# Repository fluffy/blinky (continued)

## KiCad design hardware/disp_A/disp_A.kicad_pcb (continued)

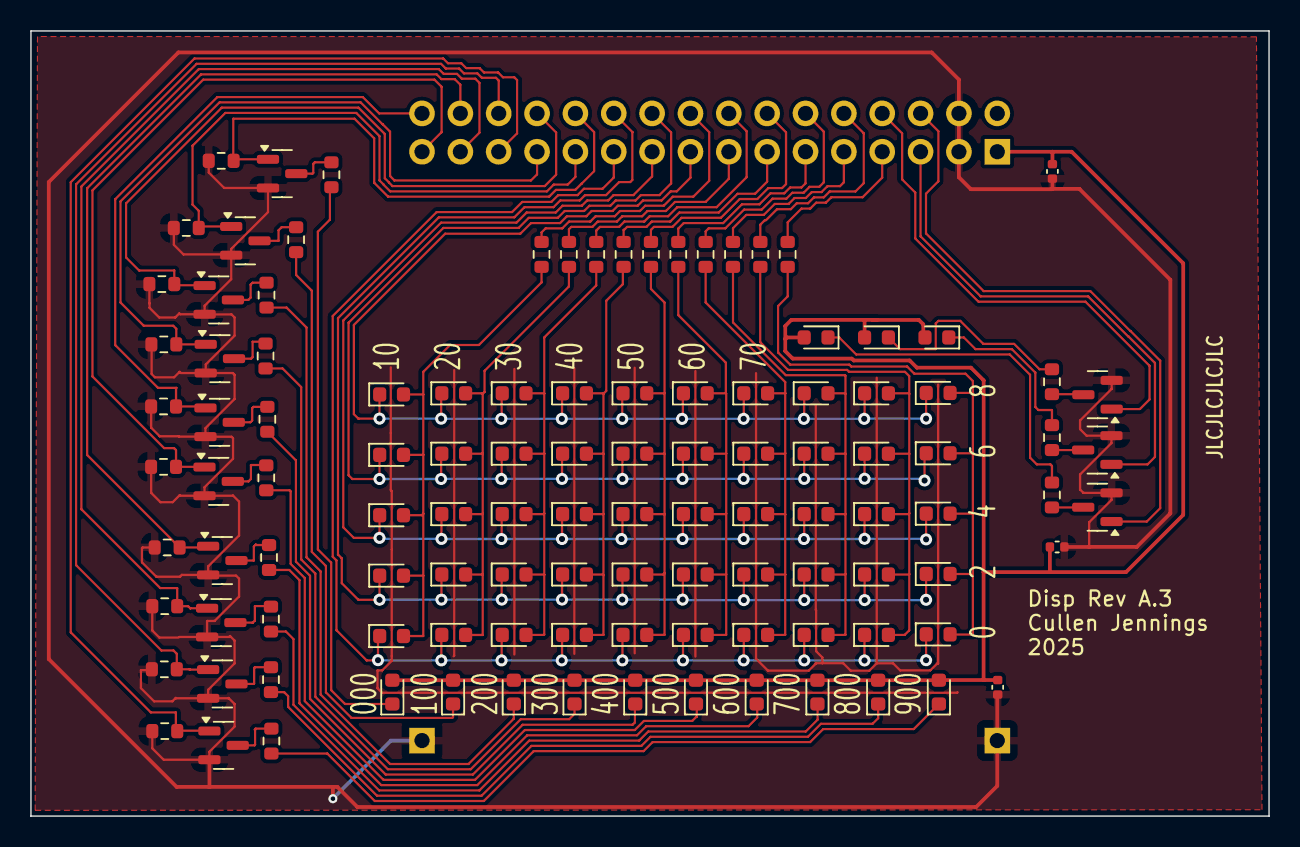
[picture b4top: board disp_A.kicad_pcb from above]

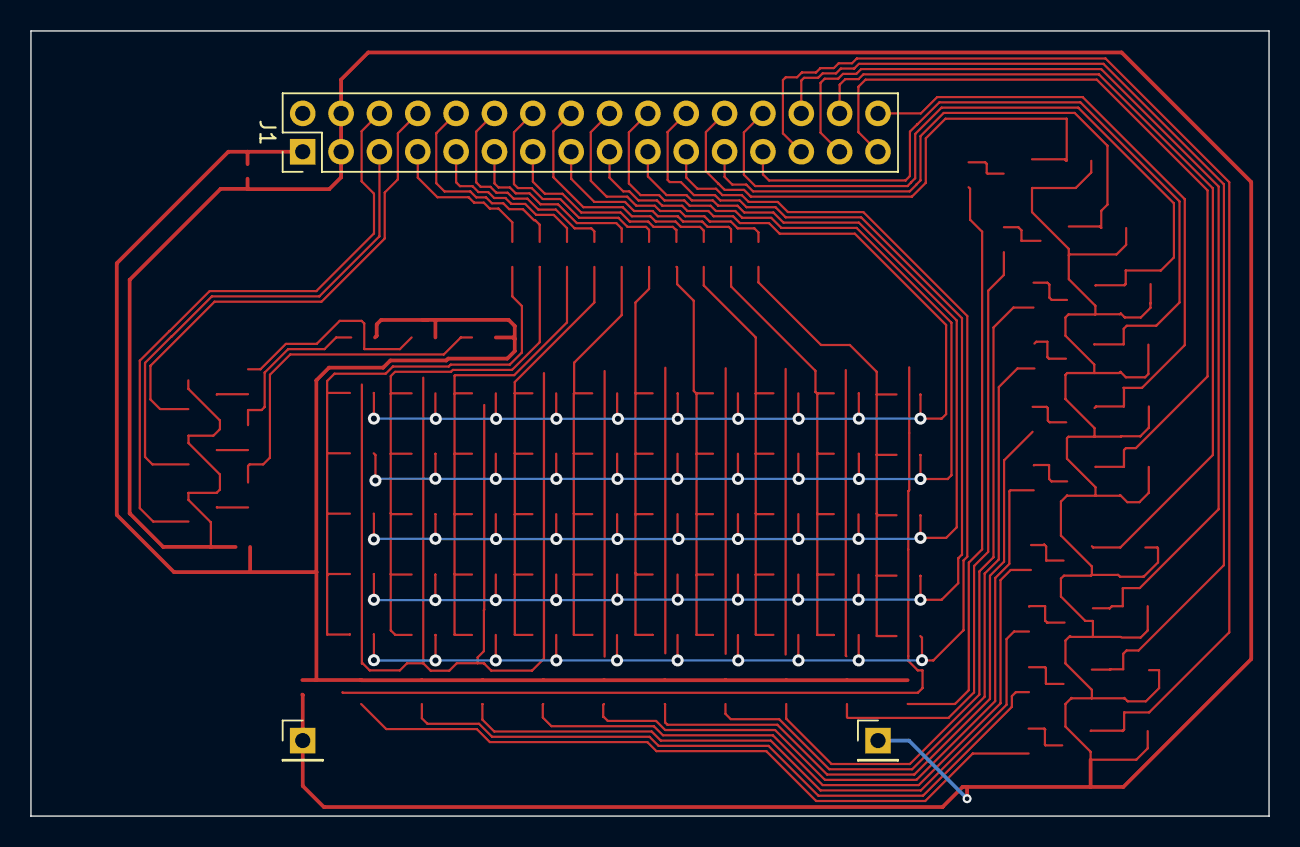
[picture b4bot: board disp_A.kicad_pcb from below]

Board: 2 copper layers, 82.0 x 52.0 mm, 115 parts (3 on the bottom side), 66 nets.

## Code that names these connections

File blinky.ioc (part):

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Mcu.Name=STM32F405RGTx
Mcu.Package=LQFP64
Mcu.UserName=STM32F405RGTx
PA0-WKUP.GPIOParameters=GPIO_Label
PA0-WKUP.GPIO_Label=AUX_CLK
PA0-WKUP.Signal=S_TIM5_CH1
PA1.GPIOParameters=GPIO_Label
PA1.GPIO_Label=AUX_GPS_PPS
PA1.Signal=S_TIM5_CH2
PA10.GPIOParameters=GPIO_Speed,GPIO_Label
PA10.GPIO_Label=USB_TX
PA10.GPIO_Speed=GPIO_SPEED_FREQ_HIGH
PA10.Mode=Asynchronous
PA10.Signal=USART1_RX
PA11.GPIOParameters=PinState,GPIO_Label
PA11.GPIO_Label=LEDMG
PA11.PinState=GPIO_PIN_SET
PA11.Signal=GPIO_Output
PA12.GPIOParameters=PinState,GPIO_Label
PA12.GPIO_Label=LEDMR
PA12.PinState=GPIO_PIN_RESET
PA12.Signal=GPIO_Output
PA13.GPIOParameters=GPIO_Label
PA13.GPIO_Label=SWDIO
PA13.Mode=Serial_Wire
PA13.Signal=SYS_JTMS-SWDIO
PA14.GPIOParameters=GPIO_Label
PA14.GPIO_Label=SWDCLK
PA14.Mode=Serial_Wire
PA14.Signal=SYS_JTCK-SWCLK
PA15.GPIOParameters=GPIO_Label
PA15.GPIO_Label=CLK
PA15.Signal=S_TIM2_CH1_ETR
PA2.GPIOParameters=GPIO_Label
PA2.GPIO_Label=AUX_SYNC_MON
PA2.Signal=S_TIM5_CH3
PA3.GPIOParameters=PinState,GPIO_PuPd,GPIO_Label
PA3.GPIO_Label=LED4
PA3.GPIO_PuPd=GPIO_NOPULL
PA3.PinState=GPIO_PIN_RESET
PA3.Signal=GPIO_Output
PA4.GPIOParameters=GPIO_Label
PA4.GPIO_Label=OSC_ADJ
PA4.Signal=COMP_DAC1_group
PA5.GPIOParameters=GPIO_Label
PA5.GPIO_Label=AUD_OUT
PA5.Signal=COMP_DAC2_group
PA6.GPIOParameters=GPIO_Label
PA6.GPIO_Label=LED1
PA6.Signal=GPIO_Output
PA7.GPIOParameters=GPIO_Label
PA7.GPIO_Label=LED2
PA7.Signal=ADCx_IN7
PA8.GPIOParameters=GPIO_Label
PA8.GPIO_Label=SYNC_OUT
PA8.Signal=S_TIM1_CH1
PA9.GPIOParameters=GPIO_Speed,GPIO_Label
PA9.GPIO_Label=USB_RX
PA9.GPIO_Speed=GPIO_SPEED_FREQ_HIGH
PA9.Mode=Asynchronous
PA9.Signal=USART1_TX
PB0.GPIOParameters=PinState,GPIO_Label
PB0.GPIO_Label=LED9
PB0.PinState=GPIO_PIN_SET
PB0.Signal=GPIO_Output
PB1.GPIOParameters=PinState,GPIO_Label
PB1.GPIO_Label=LED10
PB1.PinState=GPIO_PIN_SET
PB1.Signal=GPIO_Output
PB10.GPIOParameters=GPIO_Label
PB10.GPIO_Label=GPS_PPS
PB10.Signal=S_TIM2_CH3
PB11.GPIOParameters=GPIO_Label
PB11.GPIO_Label=SYNC_MON
PB11.Signal=S_TIM2_CH4
PB12.GPIOParameters=GPIO_Label
PB12.GPIO_Label=NCOL8
PB12.Signal=GPIO_Output
PB13.GPIOParameters=GPIO_Label
PB13.GPIO_Label=NCOL7
PB13.Signal=GPIO_Output
PB14.GPIOParameters=GPIO_Label
PB14.GPIO_Label=NCOL6
PB14.Signal=GPIO_Output
PB15.GPIOParameters=GPIO_Label
PB15.GPIO_Label=NCOL5
PB15.Signal=GPIO_Output
PB2.GPIOParameters=GPIO_PuPd,GPIO_Label
PB2.GPIO_Label=BOOT1
PB2.GPIO_PuPd=GPIO_PULLDOWN
PB2.Signal=GPIO_Input
PB3.GPIOParameters=GPIO_Label
PB3.GPIO_Label=SYNC_IN
PB3.Signal=S_TIM2_CH2
PB4.GPIOParameters=GPIO_PuPd,GPIO_Label
PB4.GPIO_Label=LED3
PB4.GPIO_PuPd=GPIO_PULLDOWN
PB4.Signal=GPIO_Input
PB5.GPIOParameters=GPIO_Speed,GPIO_Label
PB5.GPIO_Label=NROW5
PB5.GPIO_Speed=GPIO_SPEED_FREQ_LOW
PB5.Signal=GPIO_Output
PB6.GPIOParameters=GPIO_Label
PB6.GPIO_Label=NCOL1
PB6.Signal=GPIO_Output
PB7.GPIOParameters=GPIO_Label
PB7.GPIO_Label=LEDMB
PB7.Signal=GPIO_Output
PB8.GPIOParameters=GPIO_Label
PB8.GPIO_Label=SCL
PB8.Mode=I2C
PB8.Signal=I2C1_SCL
PB9.GPIOParameters=GPIO_Label
PB9.GPIO_Label=SDA
PB9.Mode=I2C
PB9.Signal=I2C1_SDA
PC0.GPIOParameters=GPIO_Label
PC0.GPIO_Label=AUD_IN
PC0.Signal=ADCx_IN10
PC1.GPIOParameters=GPIO_Label
PC1.GPIO_Label=NROW2
PC1.Signal=GPIO_Output
PC10.GPIOParameters=GPIO_Speed,GPIO_Label
PC10.GPIO_Label=GPS_RX1
PC10.GPIO_Speed=GPIO_SPEED_FREQ_HIGH
PC10.Mode=Asynchronous
PC10.Signal=USART3_TX
PC11.GPIOParameters=GPIO_Speed,GPIO_Label
PC11.GPIO_Label=GPS_TX1
PC11.GPIO_Speed=GPIO_SPEED_FREQ_HIGH
PC11.Mode=Asynchronous
PC11.Signal=USART3_RX
PC12.GPIOParameters=GPIO_Speed,GPIO_Label
PC12.GPIO_Label=NCOL9
PC12.GPIO_Speed=GPIO_SPEED_FREQ_LOW
PC12.Signal=GPIO_Output
PC13-ANTI_TAMP.GPIOParameters=GPIO_PuPd,GPIO_Label
PC13-ANTI_TAMP.GPIO_Label=BTN1
PC13-ANTI_TAMP.GPIO_PuPd=GPIO_PULLDOWN
PC13-ANTI_TAMP.Signal=GPIO_Input
PC14-OSC32_IN.GPIOParameters=PinState,GPIO_PuPd,GPIO_Label
PC14-OSC32_IN.GPIO_Label=NCOL10
PC14-OSC32_IN.GPIO_PuPd=GPIO_NOPULL
PC14-OSC32_IN.PinState=GPIO_PIN_RESET
PC14-OSC32_IN.Signal=GPIO_Output
PC15-OSC32_OUT.GPIOParameters=PinState,GPIO_PuPd,GPIO_Label
PC15-OSC32_OUT.GPIO_Label=NROW1
PC15-OSC32_OUT.GPIO_PuPd=GPIO_NOPULL
PC15-OSC32_OUT.PinState=GPIO_PIN_RESET
PC15-OSC32_OUT.Signal=GPIO_Output
PC2.GPIOParameters=GPIO_Label
PC2.GPIO_Label=NROW3
PC2.Signal=GPIO_Output
PC3.GPIOParameters=GPIO_Label
PC3.GPIO_Label=NROW4
PC3.Signal=GPIO_Output
PC4.GPIOParameters=GPIO_Label
PC4.GPIO_Label=LED7
PC4.Signal=GPIO_Output
PC5.GPIOParameters=PinState,GPIO_Label
PC5.GPIO_Label=LED8
PC5.PinState=GPIO_PIN_SET
PC5.Signal=GPIO_Output
PC6.GPIOParameters=GPIO_Label
PC6.GPIO_Label=AUX_SYNC_IN
PC6.Signal=S_TIM8_CH1
PC7.GPIOParameters=GPIO_Label
PC7.GPIO_Label=NCOL4
PC7.Signal=GPIO_Output
PC8.GPIOParameters=GPIO_Label
PC8.GPIO_Label=NCOL3
PC8.Signal=GPIO_Output
PC9.GPIOParameters=GPIO_Label
PC9.GPIO_Label=NCOL2
PC9.Signal=GPIO_Output
PD2.GPIOParameters=GPIO_Speed,GPIO_Label
PD2.GPIO_Label=DB3
PD2.GPIO_Speed=GPIO_SPEED_FREQ_HIGH
PD2.Signal=GPIO_Output
PH0-OSC_IN.GPIOParameters=GPIO_Label
PH0-OSC_IN.GPIO_Label=HSE_IN
PH0-OSC_IN.Mode=HSE-External-Oscillator
PH0-OSC_IN.Signal=RCC_OSC_IN
PH1-OSC_OUT.GPIOParameters=GPIO_Label
PH1-OSC_OUT.GPIO_Label=HSE_OUT
PH1-OSC_OUT.Mode=HSE-External-Oscillator
PH1-OSC_OUT.Signal=RCC_OSC_OUT
RCC.HSE_VALUE=16000000
RCC.SYSCLKFreq_VALUE=168000000
RCC.SYSCLKSource=RCC_SYSCLKSOURCE_PLLCLK
board=custom

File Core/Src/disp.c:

// SPDX-FileCopyrightText: Copyright (c) 2023 Cullen Jennings
// SPDX-License-Identifier: BSD-2-Clause

#include "disp.h"

#include <stdbool.h>
#include <stdint.h>
#include <stdio.h>
#include <stm32f4xx_ll_tim.h>
#include <string.h>

#include "config.h"
#include "hardware.h"
#include "main.h"
#include "measurement.h"
#include "setting.h"

void dispInit() {
  // nothing to do here
}

void dispSetup() {
  if (config.product != 1) {
    return;
  }

  GPIO_InitTypeDef GPIO_InitStruct = {0};

  HAL_GPIO_DeInit(LED2_GPIO_Port, LED2_Pin);
  GPIO_InitStruct.Pin = LED2_Pin;
  GPIO_InitStruct.Mode = GPIO_MODE_OUTPUT_PP;
  GPIO_InitStruct.Pull = GPIO_NOPULL;
  GPIO_InitStruct.Speed = GPIO_SPEED_FREQ_LOW;
  HAL_GPIO_Init(LED2_GPIO_Port, &GPIO_InitStruct);

  HAL_GPIO_DeInit(LED3_GPIO_Port, LED3_Pin);
  GPIO_InitStruct.Pin = LED3_Pin;
  GPIO_InitStruct.Mode = GPIO_MODE_OUTPUT_PP;
  GPIO_InitStruct.Pull = GPIO_NOPULL;
  GPIO_InitStruct.Speed = GPIO_SPEED_FREQ_LOW;
  HAL_GPIO_Init(LED3_GPIO_Port, &GPIO_InitStruct);

  HAL_GPIO_DeInit(LED5_GPIO_Port, LED5_Pin);
  GPIO_InitStruct.Pin = LED5_Pin;
  GPIO_InitStruct.Mode = GPIO_MODE_OUTPUT_PP;
  GPIO_InitStruct.Pull = GPIO_NOPULL;
  GPIO_InitStruct.Speed = GPIO_SPEED_FREQ_LOW;
  HAL_GPIO_Init(LED5_GPIO_Port, &GPIO_InitStruct);

  HAL_GPIO_DeInit(LED6_GPIO_Port, LED6_Pin);
  GPIO_InitStruct.Pin = LED6_Pin;
  GPIO_InitStruct.Mode = GPIO_MODE_OUTPUT_PP;
  GPIO_InitStruct.Pull = GPIO_NOPULL;
  GPIO_InitStruct.Speed = GPIO_SPEED_FREQ_LOW;
  HAL_GPIO_Init(LED6_GPIO_Port, &GPIO_InitStruct);

  HAL_GPIO_WritePin(LED1_GPIO_Port, LED1_Pin, GPIO_PIN_RESET);
  HAL_GPIO_WritePin(LED2_GPIO_Port, LED2_Pin, GPIO_PIN_RESET);
  HAL_GPIO_WritePin(LED3_GPIO_Port, LED3_Pin, GPIO_PIN_RESET);
  HAL_GPIO_WritePin(LED4_GPIO_Port, LED4_Pin, GPIO_PIN_RESET);
#if 1  // TODO - still no use onv v10hw
  HAL_GPIO_WritePin(LED5_GPIO_Port, LED5_Pin, GPIO_PIN_RESET);
  HAL_GPIO_WritePin(LED6_GPIO_Port, LED6_Pin, GPIO_PIN_RESET);
#endif
  HAL_GPIO_WritePin(LED7_GPIO_Port, LED7_Pin, GPIO_PIN_RESET);
  HAL_GPIO_WritePin(LED8_GPIO_Port, LED8_Pin, GPIO_PIN_RESET);
  HAL_GPIO_WritePin(LED9_GPIO_Port, LED9_Pin, GPIO_PIN_RESET);
  HAL_GPIO_WritePin(LED10_GPIO_Port, LED10_Pin, GPIO_PIN_RESET);
}

void dispUpdate(int32_t dispUs, int32_t dispS) {
  if (config.product != 1) {
    return;
  }

  // called in an interupt - keep this fast
  int32_t ledMs = dispUs / 1000l;

  if (setting.blinkDispAudio) {
    ledMs = data.blinkAudioDelayMs;
  }

  if (ledMs >= 1000) {
    ledMs -= 1000;
  }

#if 0
    // this shows 2 ms times to 1 second
    int16_t binCount =  1  << (9 - (ledMs / 100)%10) ;  // 100 ms
    int row = 5 - (ledMs / 2) % 5;     // 2 ms across
    int col = 10 - (ledMs / 10) % 10;  // 10 ms down
#else
  // this shows 30 * 4 fps frame times
  int blinks = (ledMs * 3);                            // 3000 blinks per second
  int16_t binCount = 1 << (9 - (blinks / 1000) % 10);  // 3 fps
  int row = 5 - (blinks / 25) % 4;                     // 120 fps across 4 leds
  int col = 10 - (blinks / 100) % 10;                  // 30 fps
#endif

  if (setting.blinkBlank) {
    binCount = 0x1000;
    row = 255;
    col = 255;
  }

  if (setting.blinkHaveDisplay) {
    HAL_GPIO_WritePin(NCOL1_GPIO_Port, NCOL1_Pin,
                      (col == 1) ? GPIO_PIN_SET : GPIO_PIN_RESET);
    HAL_GPIO_WritePin(NCOL2_GPIO_Port, NCOL2_Pin,
                      (col == 2) ? GPIO_PIN_SET : GPIO_PIN_RESET);
    HAL_GPIO_WritePin(NCOL3_GPIO_Port, NCOL3_Pin,
                      (col == 3) ? GPIO_PIN_SET : GPIO_PIN_RESET);
    HAL_GPIO_WritePin(NCOL4_GPIO_Port, NCOL4_Pin,
                      (col == 4) ? GPIO_PIN_SET : GPIO_PIN_RESET);
    HAL_GPIO_WritePin(NCOL5_GPIO_Port, NCOL5_Pin,
                      (col == 5) ? GPIO_PIN_SET : GPIO_PIN_RESET);
    HAL_GPIO_WritePin(NCOL6_GPIO_Port, NCOL6_Pin,
                      (col == 6) ? GPIO_PIN_SET : GPIO_PIN_RESET);
    HAL_GPIO_WritePin(NCOL7_GPIO_Port, NCOL7_Pin,
                      (col == 7) ? GPIO_PIN_SET : GPIO_PIN_RESET);
    HAL_GPIO_WritePin(NCOL8_GPIO_Port, NCOL8_Pin,
                      (col == 8) ? GPIO_PIN_SET : GPIO_PIN_RESET);
    HAL_GPIO_WritePin(NCOL9_GPIO_Port, NCOL9_Pin,
                      (col == 9) ? GPIO_PIN_SET : GPIO_PIN_RESET);
    HAL_GPIO_WritePin(NCOL10_GPIO_Port, NCOL10_Pin,
                      (col == 10) ? GPIO_PIN_SET : GPIO_PIN_RESET);

    HAL_GPIO_WritePin(NROW1_GPIO_Port, NROW1_Pin,
                      (row == 1) ? GPIO_PIN_RESET : GPIO_PIN_SET);
    HAL_GPIO_WritePin(NROW2_GPIO_Port, NROW2_Pin,
                      (row == 2) ? GPIO_PIN_RESET : GPIO_PIN_SET);
    HAL_GPIO_WritePin(NROW3_GPIO_Port, NROW3_Pin,
                      (row == 3) ? GPIO_PIN_RESET : GPIO_PIN_SET);
    HAL_GPIO_WritePin(NROW4_GPIO_Port, NROW4_Pin,
                      (row == 4) ? GPIO_PIN_RESET : GPIO_PIN_SET);
    HAL_GPIO_WritePin(NROW5_GPIO_Port, NROW5_Pin,
                      (row == 5) ? GPIO_PIN_RESET : GPIO_PIN_SET);
  }

  if (setting.blinkHaveDisplay) {
    // Low 4 bits of display
    HAL_GPIO_WritePin(LED1_GPIO_Port, LED1_Pin,
                      (binCount & 0x01) ? GPIO_PIN_SET : GPIO_PIN_RESET);
    HAL_GPIO_WritePin(LED2_GPIO_Port, LED2_Pin,
                      (binCount & 0x02) ? GPIO_PIN_SET : GPIO_PIN_RESET);
    HAL_GPIO_WritePin(LED3_GPIO_Port, LED3_Pin,
                      (binCount & 0x04) ? GPIO_PIN_SET : GPIO_PIN_RESET);
    HAL_GPIO_WritePin(LED4_GPIO_Port, LED4_Pin,
                      (binCount & 0x08) ? GPIO_PIN_SET : GPIO_PIN_RESET);

    // High 4 bits of display
#if 1  // TODO - still not use on V10 hw
    // problems LED 5,6 input only
    HAL_GPIO_WritePin(LED5_GPIO_Port, LED5_Pin,
                      (binCount & 0x10) ? GPIO_PIN_SET : GPIO_PIN_RESET);
    HAL_GPIO_WritePin(LED6_GPIO_Port, LED6_Pin,
                      (binCount & 0x20) ? GPIO_PIN_SET : GPIO_PIN_RESET);
#endif

    HAL_GPIO_WritePin(LED7_GPIO_Port, LED7_Pin,
                      (binCount & 0x40) ? GPIO_PIN_SET : GPIO_PIN_RESET);
    HAL_GPIO_WritePin(LED8_GPIO_Port, LED8_Pin,
                      (binCount & 0x80) ? GPIO_PIN_SET : GPIO_PIN_RESET);

    HAL_GPIO_WritePin(LED9_GPIO_Port, LED9_Pin,
                      (binCount & 0x100) ? GPIO_PIN_SET : GPIO_PIN_RESET);
    HAL_GPIO_WritePin(LED10_GPIO_Port, LED10_Pin,
                      (binCount & 0x200) ? GPIO_PIN_SET : GPIO_PIN_RESET);
  }
}

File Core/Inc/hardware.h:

// SPDX-FileCopyrightText: Copyright (c) 2023 Cullen Jennings
// SPDX-License-Identifier: BSD-2-Clause

#pragma once

#include <stm32f4xx_ll_tim.h>

extern I2C_HandleTypeDef hi2c1;

extern TIM_HandleTypeDef htim1;
extern TIM_HandleTypeDef htim2;
extern TIM_HandleTypeDef htim3;
extern TIM_HandleTypeDef htim4;
extern TIM_HandleTypeDef htim5;
extern TIM_HandleTypeDef htim6;
extern TIM_HandleTypeDef htim8;

extern UART_HandleTypeDef huart1;
extern UART_HandleTypeDef huart3;

extern ADC_HandleTypeDef hadc1;
extern ADC_HandleTypeDef hadc2;
extern DAC_HandleTypeDef hdac;

#define hADC hadc1

#define hDAC hdac
#define DAC_CH_OSC_ADJ DAC_CHANNEL_1
#define DAC_CH_AUD_OUT DAC_CHANNEL_2

#define hI2c hi2c1
#define hUartDebug huart1
#define hUartGps huart3
#define USART_GPS USART3

#define hTimePps htim1
#define TimePps_CH_SYNC_OUT TIM_CHANNEL_1
#define TimePps_LL_CH_SYNC_OUT LL_TIM_CHANNEL_CH1

#define hTimeSync htim2
#define TimeSync_CH_SYNC_IN TIM_CHANNEL_2
#define TimeSync_HAL_CH_SYNC_IN HAL_TIM_ACTIVE_CHANNEL_2
#define TimeSync_CH_GPS_PPS TIM_CHANNEL_3
#define TimeSync_HAL_CH_GPS_PPS HAL_TIM_ACTIVE_CHANNEL_3
#define TimeSync_CH_SYNC_MON TIM_CHANNEL_4
#define TimeSync_HAL_CH_SYNC_MON HAL_TIM_ACTIVE_CHANNEL_4

#define hTimeADC htim3

#define hTimeBlink htim4

#define hTimeAux htim5
#define TimeAux_CH_AUX_CLK TIM_CHANNEL_1
#define TimeAux_CH_GPS_PPS TIM_CHANNEL_2
#define TimeAux_HAL_CH_GPS_PPS HAL_TIM_ACTIVE_CHANNEL_3
#define TimeAux_CH_SYNC_MON TIM_CHANNEL_3
#define TimeAux_HAL_CH_SYNC_MON HAL_TIM_ACTIVE_CHANNEL_3

#define hTimeDAC htim6

#define hTimeLtc htim8
#define TimeLtc_CH_SYNC_IN2 TIM_CHANNEL_1
#define TimeLtc_HAL_CH_SYNC_IN2 HAL_TIM_ACTIVE_CHANNEL_1

#define LED6_Pin GPS_RX1_Pin
#define LED6_GPIO_Port GPS_RX1_GPIO_Port
#define LED5_Pin GPS_TX1_Pin
#define LED5_GPIO_Port GPS_TX1_GPIO_Port
#define BTN2_Pin GPS_PPS_Pin
#define BTN2_GPIO_Port GPS_PPS_GPIO_Port
#define BTN3_Pin BOOT1_Pin
#define BTN3_GPIO_Port BOOT1_GPIO_Port

void Error_Handler();

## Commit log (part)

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2023-12-30 set up eeprom form serial #9
2023-12-30 print phases of inputs
2023-12-30 clean up time print display and sync
2023-12-30 update version
2023-12-30 clean up formatting
2023-12-30 long history for ppb
2024-01-01 redo version
2024-01-02 clean up sync and calculating total seconds
2024-01-03 program board serial #10
2024-01-03 up version
2024-01-04 update stm32flash line to be correct
2024-01-04 update printouts
2024-01-04 update CH340 datasheet to english
2024-01-04 cleanup existing schematic
2024-01-04 start new switch regulator layout
2024-01-05 start 2nd supply
2024-01-05 clean up
2024-01-05 add yet antoehr power connector
2024-01-05 send off 9.3 version of power board
2024-01-05 gps sync going
2024-01-05 sync to PPS input
2024-01-05 sync LTC with GPS
2024-01-05 ltc time synced up in and out
2024-01-05 refactor case
2024-01-05 reflow
2024-01-05 sync ext when have gps or ltc
2024-01-05 set status LED based on sync
2024-01-05 validate sync
2024-01-06 start debug of problem where get out of sync for a cycle
2024-01-06 start 9.4 power supply test
2024-01-06 clean up simple 9.4 for new power supply
2024-01-06 do v9.4 board with new power reg
2024-01-06 submitted version of 9.4 board
2024-01-07 Fix bug with loosing last transition of LTC
2024-01-07 turn off broken ppm and pbm code
2024-01-07 added PPS mode
2024-01-07 new config format with space for PPS mode config
2024-01-07 updated calbration for v9 boards
2024-01-07 fix clock 9.4 for rotations that JLCPCB found after I submitted
2024-01-08 add .editorconfig
2024-01-09 migrate to latest cube
2024-01-09 changes to move to cmake
2024-01-09 remove old make stuff
2024-01-09 add openocd open ocd open-ocd config file
2024-01-10 clean up detection of having sync and loosing sync
2024-01-10 update readme for cmake
2024-01-10 upgrade clion
2024-01-10 start clock v10.0
2024-01-10 start disp V10.0 HW
2024-01-10 start blink 10.0 hw
2024-01-10 Fixes #259 pwrd on gpx rx
2024-01-10 Fixes #211 led setting when not running
2024-01-11 change temp sensor to to TMP112A
2024-01-12 change LEDMY to LEDMB. Fixes #230
2024-01-13 update version and ingores
2024-01-13 update calbration for #7 with 2Mhz osc
2024-01-13 update syncValidTimeSeconds
2024-01-13 add datashee for oven controlled oscilator
2024-01-14 add design for box ends
2024-01-15 start seperation of disp code
2024-01-15 seperate out disp code
2024-01-15 fix up setting linking
2024-01-21 update to fix link problems from refactor
2024-01-21 update for serial program
2024-01-22 update serial program notes
2024-01-23 clean up LED5/6 problem and BTN2
2024-01-23 fix buttons. Fixes #264 Fixes #261
2024-01-23 fix up layout on clock
2024-01-23 add current sense resistor to clock 3.3V
2024-01-23 add a sense resistor to blink v10
2024-01-23 add sense resitors to other ps on bink
2024-01-24 replace power selection diodes with ideal diodes
2024-01-24 start adding reset circuit to v10 blink
2024-01-24 start adding boost powere supply
2024-01-25 sorting out blink 10 schematic
2024-01-25 starting part placment blink 10
2024-01-25 update reset boot on clock v10
2024-01-25 fix up ground on clock v10
2024-01-26 Add PP/LTC Jumper Fixes #275
2024-01-26 add power sense resisitors Fixes #294
2024-01-26 add jumper for USB / Reset disconnect Fixes #293
2024-01-26 moved to 250mW resisotrs. Fixes #289
2024-01-26 fiux voltage dirvide for GPS TX. Fixes #260
2024-01-26 update version with CLion
2024-01-26 fix up clock board errors
2024-01-27 route blink v10 board
2024-01-27 clean up PCB
2024-01-27 clean up blink pcb
2024-01-27 blink board ready for v10
2024-01-28 version of blink submitted for hw v10.0
2024-01-28 version submitted of disp v10.0 hardware
2024-01-28 remove the connector offset
2024-01-28 add pins for other osc
2024-01-28 thicker 5V power distribution
2024-01-28 clean up clock v10 PCB
2024-01-28 version of clock harrdware V10.0
2024-01-28 update wishlist
2024-01-29 update with production pick and place changes
2024-01-30 adjust version
2024-01-30 add SPDX headers
2024-02-01 start blink v11 hw
2024-02-02 start clock v11 hw
2024-02-06 start changes for V10 clock pin outs
2024-02-06 more changes for V10 clock pins
2024-02-06 add 2nd ADC for USB power sense
2024-02-06 fix tyupo
2024-02-06 add todo
2024-02-06 updating pins
2024-02-06 move button conde to it's own file
2024-02-07 start adding power managment
2024-02-09 move phase info into settings
2024-02-09 move clock ration settings into settings
2024-02-09 program serial number 13
2024-02-09 fix typo
2024-02-09 fix but on adc1 for power detection
2024-02-09 correctly detect USB power available
2024-02-10 update power handling
2024-02-10 start of blink v10 config
2024-02-10 add deinit to buttons
2024-02-10 correct pin names
2024-02-10 buttons working on display board
2024-02-10 disp working v10 blink hw
2024-02-10 initalize clock board #15
2024-02-10 setup gps serial on clock board
2024-02-12 make clock board USB power only. Fixes #307
2024-02-13 update clock serial 15 to have oxco
2024-02-13 Remove R49. Fixes #303
2024-02-13 remove needless pull down reistors. Fixes #304
2024-02-15 update with sockets for differnt oscilators
2024-02-16 chance current sense resistor. Fixes#308
2024-02-18 cleaning up board
2024-02-18 clean up pcb to make more room
2024-02-19 more board cleanup
2024-02-20 start adding battery under voltageprotection UVP
2024-02-20 adding battery protection
2024-02-20 clean up for move of cpu
2024-02-21 made space for battery
2024-02-21 add test points for battery protection
2024-02-21 swap sync in / pps out
2024-02-21 fix up footprints
2024-02-22 add GPS hdr to clock board
2024-02-22 blink V11 hw hardware send to production
2024-02-22 fix rotations on blink hw V11
2024-02-23 start reorg of connectors on clock
2024-02-23 add switch to clock
2024-02-23 fixing up routing on clock
2024-02-24 clean up board
2024-02-24 update to latest CubeMX
2024-02-25 clean up clcok schematic
2024-02-25 add mount holes to clock
2024-02-25 fixed mult osc symbol error
2024-02-25 production version of clock V11 hardware
2024-02-25 start GPS variant of clock board
2024-02-25 hardsare V11 GPS board to production
2024-02-26 location confirmation for JLCPCB
2024-02-29 configured clock ev11 board ser16
2024-03-05 setup software config for GPS board
2024-03-05 add auto sync for GPS board. Fixes #312
2024-03-05 update readme for V11
2024-03-06 switch to ocxo testing
2024-03-06 fix tty to cu
2024-03-06 read LTC/PPS mode jumper
2024-03-07 move to TXCO
2024-03-08 testing battery
2024-03-10 start move to kicad8
2024-03-10 start v12 of clock and gps in kicad8
2024-03-12 start box ends in freecad
2024-03-12 ignore freecad backup files
2024-03-12 basic back end of blink box in freecad
2024-03-12 start edge cut out sides
2024-03-12 add drwawing
2024-03-25 add corner radius
2024-03-28 blink box test print 1
2024-03-28 update for correct size side offsets
2024-03-28 change view
2024-03-28 v2 print
2024-03-28 start readme for box
2024-03-30 start front of blink box
2024-03-30 add front mount holes
2024-03-30 add 3d step model export for V12 blink
2024-03-30 updates for 3d render
2024-04-01 update box
2024-04-03 fix symbol for USBLC6-2P6 that seems chaged in kicad 8
2024-04-03 fix up schematic for new USBLC6-2P6 footprint
2024-04-03 fix error on PCB from kicad8
2024-04-03 fix warnings from kicad8
2024-04-03 remove the battery protection circuit
2024-04-03 move USB connecro out 2 mm
2024-04-03 move LED over
2024-04-03 moved the test points off rails
2024-04-04 fix rotations for V12 blink
2024-04-04 blink v12 hw submitted
2024-04-05 clean up 3D files for blink board
2024-04-05 add 3D model for USB connector
2024-04-05 add 3D model for LED
2024-04-06 fixed offset for JLCPCB
2024-04-06 clean up gitignore
2024-04-09 update clock_v12 to kicad 8
2024-04-09 update on clock for kicad 8
2024-04-09 move USB on clock v12
2024-04-09 clean up 3d models for clock
2024-04-10 replace tanntium caps and start blink v13
2024-04-10 clean up version for blink v13
2024-04-14 format eeprome Serial #21 EV12 board
2024-04-14 format eeprome Serial #22 EV12 board
2024-04-27 update #21 and #22 to have TCXO
2024-04-30 updated exported pcb 3d model
2024-04-30 seperate adjustment for fron BNC offset
2024-04-30 export 3d print of parts
2024-04-30 print project for bambu
2024-05-01 adjusted hole locations
2024-05-08 update box with drawing
2024-05-10 update sizes
2024-05-11 add xcs laser file
2024-05-13 start to rename
2024-05-13 rename box file
2024-05-13 rename parts of box
2024-05-13 remove old fusion 360 files box
2024-05-13 remove old generated 3d files
2024-05-13 generated views for blink box
2024-05-13 update box readme
2024-05-14 move blink board to start RevA
2024-05-14 generate production files for blink RevA
2024-05-14 remove old versions
2024-05-15 move clock board to Rev A
2024-05-15 moved RJ45 out 2mm
2024-05-15 updarte production files for Clock board
2024-05-15 start GPS A
2024-05-15 move RJ45 on gps
2024-05-15 typo
2024-05-17 update design
2024-05-18 update JST PH S3B connector with 3D model
2024-05-18 update 3d model for 5v power reg
2024-05-18 start box for clock
2024-05-20 start edit front of clock box
2024-05-20 more edits on clock box
2024-05-21 add slot for prog connector
2024-05-22 rough outline for front place done
2024-05-22 start RJ45 location
2024-05-25 add RJ45 to clock box
2024-05-25 add USB connector slot to clock box
2024-05-25 tune up box hole locations
2024-05-26 generate the prod files for box
2024-05-26 setting up laser files
2024-05-26 update dxf files
2024-05-26 add labels
2024-05-26 set up and laser cut
2024-05-26 setup up Clock Rev A for build
2024-05-26 start Disp rev A
2024-05-26 remove old hardware files
2024-05-26 generate production files for disp board Rev A
2024-05-27 updade clock order with correct diode. Fixes #339
2024-05-27 update footprints
2024-05-27 start generation of GPS rev A.1 production files
2024-05-27 update exceptions
2024-05-27 version of GPS Rev A.1 submitted to JLCPCB
2024-05-27 updated blink productions files
2024-05-27 start hardware notes
2024-05-27 remove tal caps on GPS, clean up schamatic
2024-05-27 updadte osc footprint to use one with mount holes
2024-05-27 start making parts list for device
2024-05-27 clean up bom format
2024-05-28 fix RJ45 size in box and regen the prod files for clockA box
2024-05-28 tune up locations of wholes in blink boxA
2024-05-28 update tools in readme
2024-05-28 regen the blinkA box prod files
2024-05-28 start GpsA box
2024-05-28 generate GpsA box prod files
2024-05-28 move to one laser files for all ends
2024-05-28 update laser with updated connector locations
2024-05-29 flip blank/mute labels
2024-05-30 tune up location of holes in frames
2024-05-31 update bom list
2024-05-31 adjusted cut speeds
2024-05-31 update laser file for cut take #3
2024-05-31 get local changes
2024-05-31 set cut paramters
2024-06-09 adjust hight of USB and RJ45
2024-06-09 adding serial numbers to new boards
2024-06-09 moving blink to V A.1
2024-06-10 update blinky
2024-06-10 rename readme
2024-06-10 regen clock box prod files
2024-06-10 regen blink box prod files
2024-06-10 regen gps box prod files
2024-06-11 regen files for blink
2024-06-13 add JLC part confirmation images for blink Rev A
2024-06-16 update rotation and offsets on clock and gps
2024-06-16 Update jlc part num for CH340 Fixes#346
2024-06-16 order GPS A.2
2024-06-16 fix rotation on disp
2024-06-16 generating Clock Rev A.2
2024-06-16 updates for Clock Rev A.2
2024-06-17 update config for Rev A
2024-06-17 clarify comments
2024-06-17 images of placement mistakes from JLCPBC on Rev A.2
2024-08-24 version 1.0.240824 of software
2024-08-25 clean up notes and design info
2024-08-25 first start of manual
2024-08-25 more on manual
2024-08-25 fix typos
2024-08-25 update LICENSE for box and hardware
2024-08-25 clean up license of sub dirs
2024-08-25 reorg
2024-08-25 update license in freecad files
2024-12-07 update for new CLION
2025-06-12 update cmake
2025-06-13 updated software version
2025-06-13 allow hardware version A.2
2025-06-13 configured EEProm for some rev A devices
2025-06-15 update button colors
2025-06-15 fix formatting
2025-06-15 change defaults to audio and screen on
2025-06-15 updates for GPS Rev A.3
